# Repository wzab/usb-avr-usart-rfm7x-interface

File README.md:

usb-avr-usart-rfm7x-interface
=============================

Small interface board allowing you to control yor microcontroller wirelessly via RFM70 or RFM73 module (USART also available)

Please note, that even though my part of this design is published under permissive MIT license,
it uses some software libraries, which are published under other (e.g. GPL) license.
Please check license of every component before you reuse this design (especially for commercial puposes).

The PCB design is done so, that it may be manufactured as single-sided PCB with minimal number of jumpers.

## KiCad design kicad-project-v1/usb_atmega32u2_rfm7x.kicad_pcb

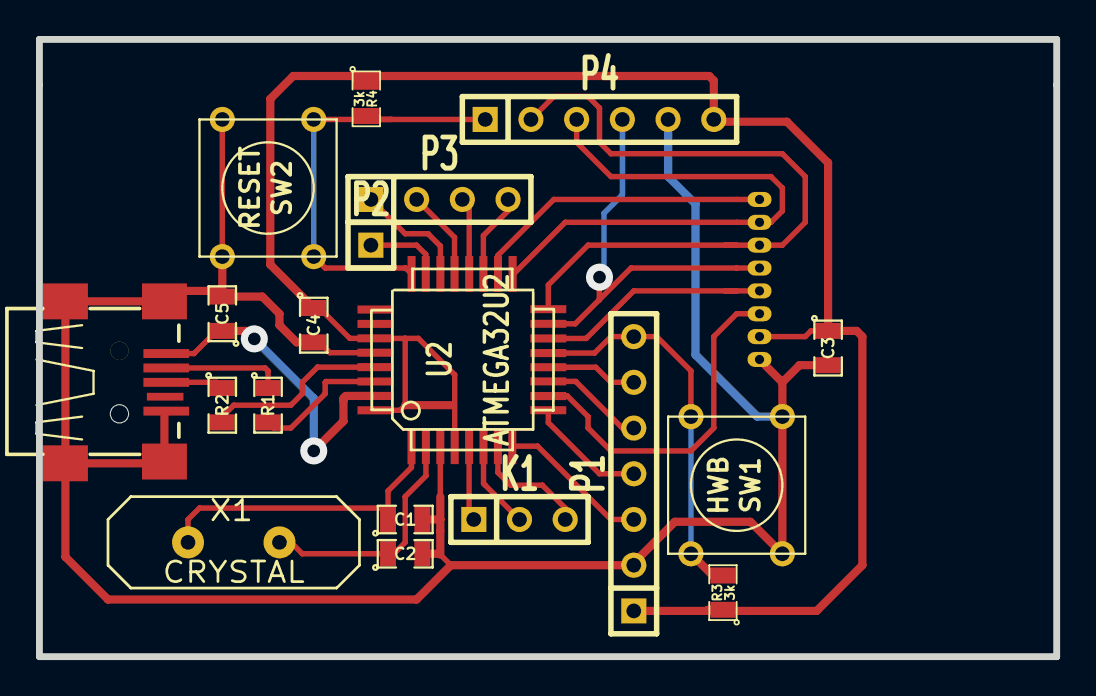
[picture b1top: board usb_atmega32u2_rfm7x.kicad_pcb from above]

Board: 2 copper layers, 56.5 x 34.3 mm, 20 parts (0 on the bottom side), 29 nets.

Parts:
C1, C2: 22pF; SM0805
C3, C4, C5: 1uF; SM0805
K1: CONN_3; SIL-3
P1: CONN_7; SIL-7
P2: CONN_1; SIL-1
P3: CONN_4; SIL-4
P4: CONN_6; SIL-6
R1, R2: 22; SM0805
R3, R4: 3k; SM0805
SW1: HWB; SW_PUSH_SMALL
SW2: RESET; SW_PUSH_SMALL
U1: RFM70/RFM73; RFM70
U2: ATMEGA32U2; TQFP32
U3: USBCONN; CONN_USB2_MiniB_SMT
X1: CRYSTAL; HC-18UV

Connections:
/MISO: P4.3, U1.2, U2.17
/MOSI: P4.2, U1.3, U2.16
/RESET: P4.1, R4.2, SW2.1, U2.24
/SCLK: P4.4, U1.4, U2.15
/VCC: C3.1, C4.1, P1.1, P4.6, R3.1, R4.1, U1.7, U2.4, U2.27, U2.32
GND: C1.2, C2.2, C3.2, C4.2, C5.2, P1.2, P4.5, SW1.1, SW2.2, U1.8, U2.3, U2.28, U3.4, U3.5
unnamed: P1.3, U2.8
unnamed: P1.4, U2.9
unnamed: P1.6, U2.12
unnamed: U1.1, U2.18
unnamed: P3.2, U2.21
unnamed: P3.1, U2.22
unnamed: P2.1, U2.23
unnamed: U1.5, U2.14
unnamed: P1.5, U2.11
unnamed: P3.4, U2.19
unnamed: R2.2, U2.29
unnamed: C5.1, U2.31, U3.1
unnamed: R1.2, U2.30
unnamed: R2.1, U3.3
unnamed: R1.1, U3.2
unnamed: C1.1, U2.1, X1.1
unnamed: K1.1, U2.5
unnamed: K1.2, U2.6
unnamed: K1.3, U2.7
unnamed: U1.6, U2.10
unnamed: P3.3, U2.20
unnamed: C2.1, U2.2, X1.2
unnamed: P1.7, R3.2, SW1.2, U2.13

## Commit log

2013-10-13 Initial commit of the kicad-project. No firmware available yet.
2013-10-13 Created folder for firmware
2013-10-13 Added programming connector
2013-10-16 small corection
2013-12-06 Added pull-up resistors on HWB and RESET lines. Changed PCB format to the new version.
2013-12-06 Converted PCB to the new format
